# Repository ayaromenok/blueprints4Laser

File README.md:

# blueprints4Laser
different blueprints

## EleksMaker A3 / OSS

[how to setup engravwer] (https://github.com/jandelgado/eleksmaker_a3)
[LaserWeb](https://github.com/LaserWeb/LaserWeb4/wiki)
[GRBL](https://github.com/gnea/grbl)

flash: `avrdude -c arduino -b 57600 -P /dev/ttyUSB0 -p atmega328p -vv -U flash:w:grbl_v1.1f.20170801.hex`

laserWeb required:
- select mashine profile: 
 tools > Machine Profile > Generik GRBL machine
 
- laser on/off setup: tools>GCODE:
   - Tool ON: S255;
   - Tool OFF: S0;

## Materials

###1.5 mm plywood

    - 800 mm/min
    - 8-10 times
    
## Parallel Line  

It should be some distance between parallel linse - LaserWeb can ignor them, if the too long (104mm is defenetly ignored)

## 3D printer software 

https://github.com/superjamie/lazyweb/wiki/3D-Printing-Control-Boards-and-Firmware
https://www.repetier-server.com/download-repetier-server/
https://reprap.org/wiki/List_of_Firmware

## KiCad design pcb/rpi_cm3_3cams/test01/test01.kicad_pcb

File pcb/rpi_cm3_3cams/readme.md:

todo: 
    - add power supply from 5V (micro-usb);
    - add one USB port(to use with usb-wifi dongle);
possible improvements:
    - HDMI;
    - GPIO;
-----------------------------------------------------
- compute module CM3+(with EMMC): DDR2 SO-DIMM
- 3 cam connectors 1x15: Cam0(2CSI Lines Cam0) and Cam1_0/Cam1_1 connected to 4CSI lines Cam1
done with KiCad 5.x
use local libs
autoreroute for kiCad 5.x.x https://www.youtube.com/watch?v=7Kk8T_bBaVY (installed in /opt/layout/bin/freeRouting.jar)

KiCad/rpi:
not integrated yet:
https://github.com/JoanTheSpark/KiCAD
https://github.com/KiCad/kicad-footprints/pull/1158

Docs:
https://www.raspberrypi.org/documentation/hardware/camera/schematics/rpi_SCH_Camera2_2p1.pdf

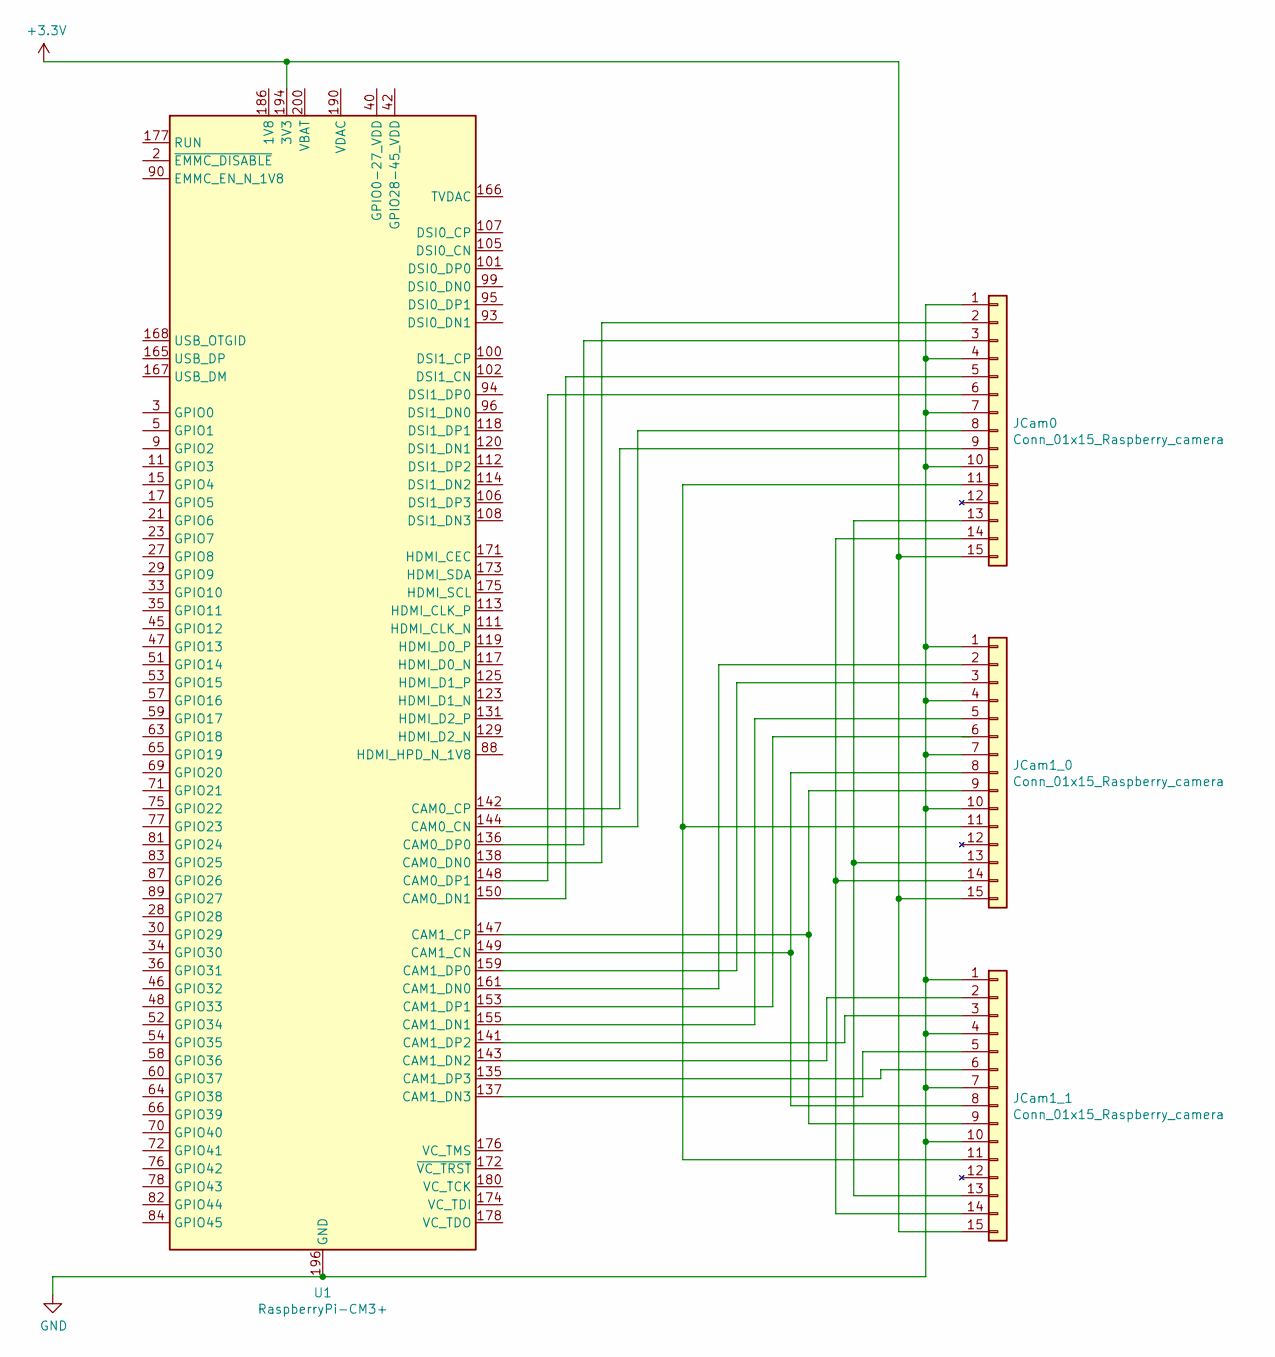
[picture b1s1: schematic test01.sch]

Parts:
JCam0, JCam1_0, JCam1_1: Conn_01x15_Raspberry_camera; Molex_200528-0150_1x15-1MP_P1.00mm_Horizontal
U1: RaspberryPi-CM3+; TE_DDR2-SODIMM-200_1473149-x_Vertical

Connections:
+3V3: JCam0.15 (3V3), JCam1_0.15 (3V3), JCam1_1.15 (3V3), U1.191 (3V3), U1.192 (3V3), U1.193 (3V3), U1.194 (3V3)
GND: JCam0.1 (gnd), JCam0.4 (gnd), JCam0.7 (gnd), JCam0.10 (gnd), JCam1_0.1 (gnd), JCam1_0.4 (gnd), JCam1_0.7 (gnd), JCam1_0.10 (gnd), JCam1_1.1 (gnd), JCam1_1.4 (gnd), JCam1_1.7 (gnd), JCam1_1.10 (gnd), U1.1 (GND), U1.7 (GND), U1.8 (GND), U1.13 (GND), U1.14 (GND), U1.19 (GND), U1.20 (GND), U1.25 (GND), U1.26 (GND), U1.31 (GND), U1.32 (GND), U1.37 (GND), U1.38 (GND), U1.43 (GND), U1.44 (GND), U1.49 (GND), U1.50 (GND), U1.55 (GND), U1.56 (GND), U1.61 (GND), U1.62 (GND), U1.67 (GND), U1.68 (GND), U1.73 (GND), U1.74 (GND), U1.79 (GND), U1.80 (GND), U1.85 (GND), U1.86 (GND), U1.91 (GND), U1.92 (GND), U1.97 (GND), U1.98 (GND), U1.103 (GND), U1.104 (GND), U1.109 (GND), U1.110 (GND), U1.115 (GND), U1.116 (GND), U1.121 (GND), U1.122 (GND), U1.127 (GND), U1.133 (GND), U1.134 (GND), U1.139 (GND), U1.140 (GND), U1.145 (GND), U1.146 (GND), U1.151 (GND), U1.152 (GND), U1.157 (GND), U1.163 (GND), U1.164 (GND), U1.169 (GND), U1.170 (GND), U1.181 (GND), U1.182 (GND), U1.187 (GND), U1.188 (GND), U1.195 (GND), U1.196 (GND)
unnamed: JCam0.2 (D0N), U1.138 (CAM0_DN0)
unnamed: JCam0.3 (D0P), U1.136 (CAM0_DP0)
unnamed: JCam0.5 (D1N), U1.150 (CAM0_DN1)
unnamed: JCam0.6 (D1P), U1.148 (CAM0_DP1)
unnamed: JCam0.8 (CLKN), U1.144 (CAM0_CN)
unnamed: JCam0.9 (CLKP), U1.142 (CAM0_CP)
unnamed: JCam0.11 (enable), JCam1_0.11 (enable), JCam1_1.11 (enable)
unnamed: JCam0.13 (SCL), JCam1_0.13 (SCL), JCam1_1.13 (SCL)
unnamed: JCam0.14 (SDA), JCam1_0.14 (SDA), JCam1_1.14 (SDA)
unnamed: JCam1_0.2 (D0N), U1.161 (CAM1_DN0)
unnamed: JCam1_0.3 (D0P), U1.159 (CAM1_DP0)
unnamed: JCam1_0.5 (D1N), U1.155 (CAM1_DN1)
unnamed: JCam1_0.6 (D1P), U1.153 (CAM1_DP1)
unnamed: JCam1_0.8 (CLKN), JCam1_1.8 (CLKN), U1.149 (CAM1_CN)
unnamed: JCam1_0.9 (CLKP), JCam1_1.9 (CLKP), U1.147 (CAM1_CP)
unnamed: JCam1_1.2 (D0N), U1.143 (CAM1_DN2)
unnamed: JCam1_1.3 (D0P), U1.141 (CAM1_DP2)
unnamed: JCam1_1.5 (D1N), U1.137 (CAM1_DN3)
unnamed: JCam1_1.6 (D1P), U1.135 (CAM1_DP3)
unnamed: U1.39 (GPIO0-27_VDD), U1.40 (GPIO0-27_VDD)
unnamed: U1.41 (GPIO28-45_VDD), U1.42 (GPIO28-45_VDD)
unnamed: U1.183 (1V8), U1.184 (1V8), U1.185 (1V8), U1.186 (1V8)
unnamed: U1.189 (VDAC), U1.190 (VDAC)
unnamed: U1.197 (VBAT), U1.198 (VBAT), U1.199 (VBAT), U1.200 (VBAT)

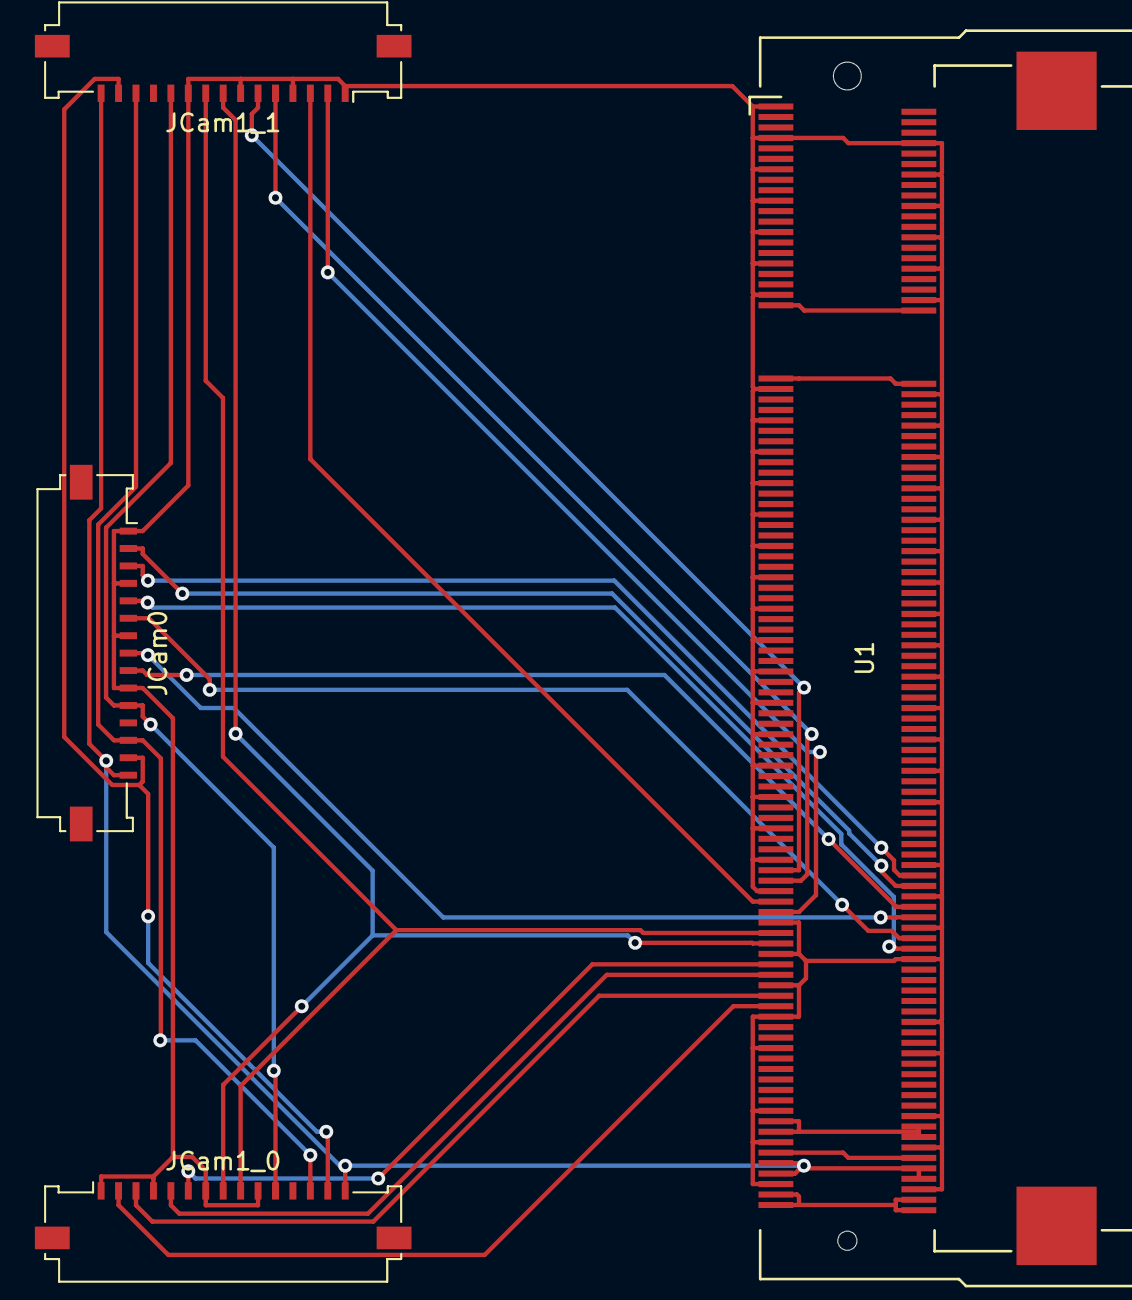
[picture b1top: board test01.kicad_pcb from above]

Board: 2 copper layers, 4 parts (0 on the bottom side), 26 nets.

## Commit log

2019-01-03 #1 backup of old 5mm box from polystyrol
2019-01-03 #1 added Waveshare RPI compute I/O board and RPI 24x25mm camera images with dimensions
2019-01-03 #1 base & camera (64+32mm) added
2019-01-03 # 1.5mm material: 0.75, 1.0, 1.25, 1.5mm test
2019-01-03 #1 updated camera plane with holes for cam.cables
2019-01-05 #2 gears plugin test
2019-01-05 #2 #3 added test for bogie(HO or 1/87 track)
2019-01-06 #2 pcb test for iron chloride
2019-01-12 EleksMaker firmware\software section added
2019-01-12 simple gears tests added to tune up LaserWeb
2019-02-06 #2 gegar version 2
2019-02-06 #2 info added
2019-02-06 #2 few more tests for 1_5mm
2019-02-07 # material tests
2019-02-13 1_5mm RPI Camv1 chassis
2019-02-18 update to std cam chassis
2019-02-18 40degree overlapped chassis added
2019-02-27 #3 airfoil sample and Clarky120mm profile added
2019-03-01 #3 update with Sg90 servo
2019-03-19 1_5mm plywood construction tests for avia
2019-03-20 #3 test output
2019-03-26 #3 test output with polylines
2019-03-26 RPiCamv1 and AGM8833 chassis
2019-03-26 # small fixes
2019-03-26 #3 eleron diitional test
2019-03-26 parallel lines issue with LaserWeb
    updates to readme.md about parallel lines issue with LaserWeb
2019-03-27 #3 fix parallel pline issue. need to make longeron about 1.5 instead of 1.4 and deeper
2019-03-27 hole position updated
2019-03-28 Final version of RpiIR and RPi stereo
2019-04-25 added info about OSS firmware for 3Dprinters
2019-04-30 added first test PCB(signals only) for Rpi CM3/ 3xCam module
2019-04-30 kiCad/Rpi3cm_3cam: absolute path updated
2019-04-30 Rpi3cm_3cam - doc added
2019-04-30 pcb: Jetson Nano doc added
2019-04-30 jetson: auvidea 6xcsi2 camera board info added
